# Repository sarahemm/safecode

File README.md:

safecode
========

SafeCode check-in system

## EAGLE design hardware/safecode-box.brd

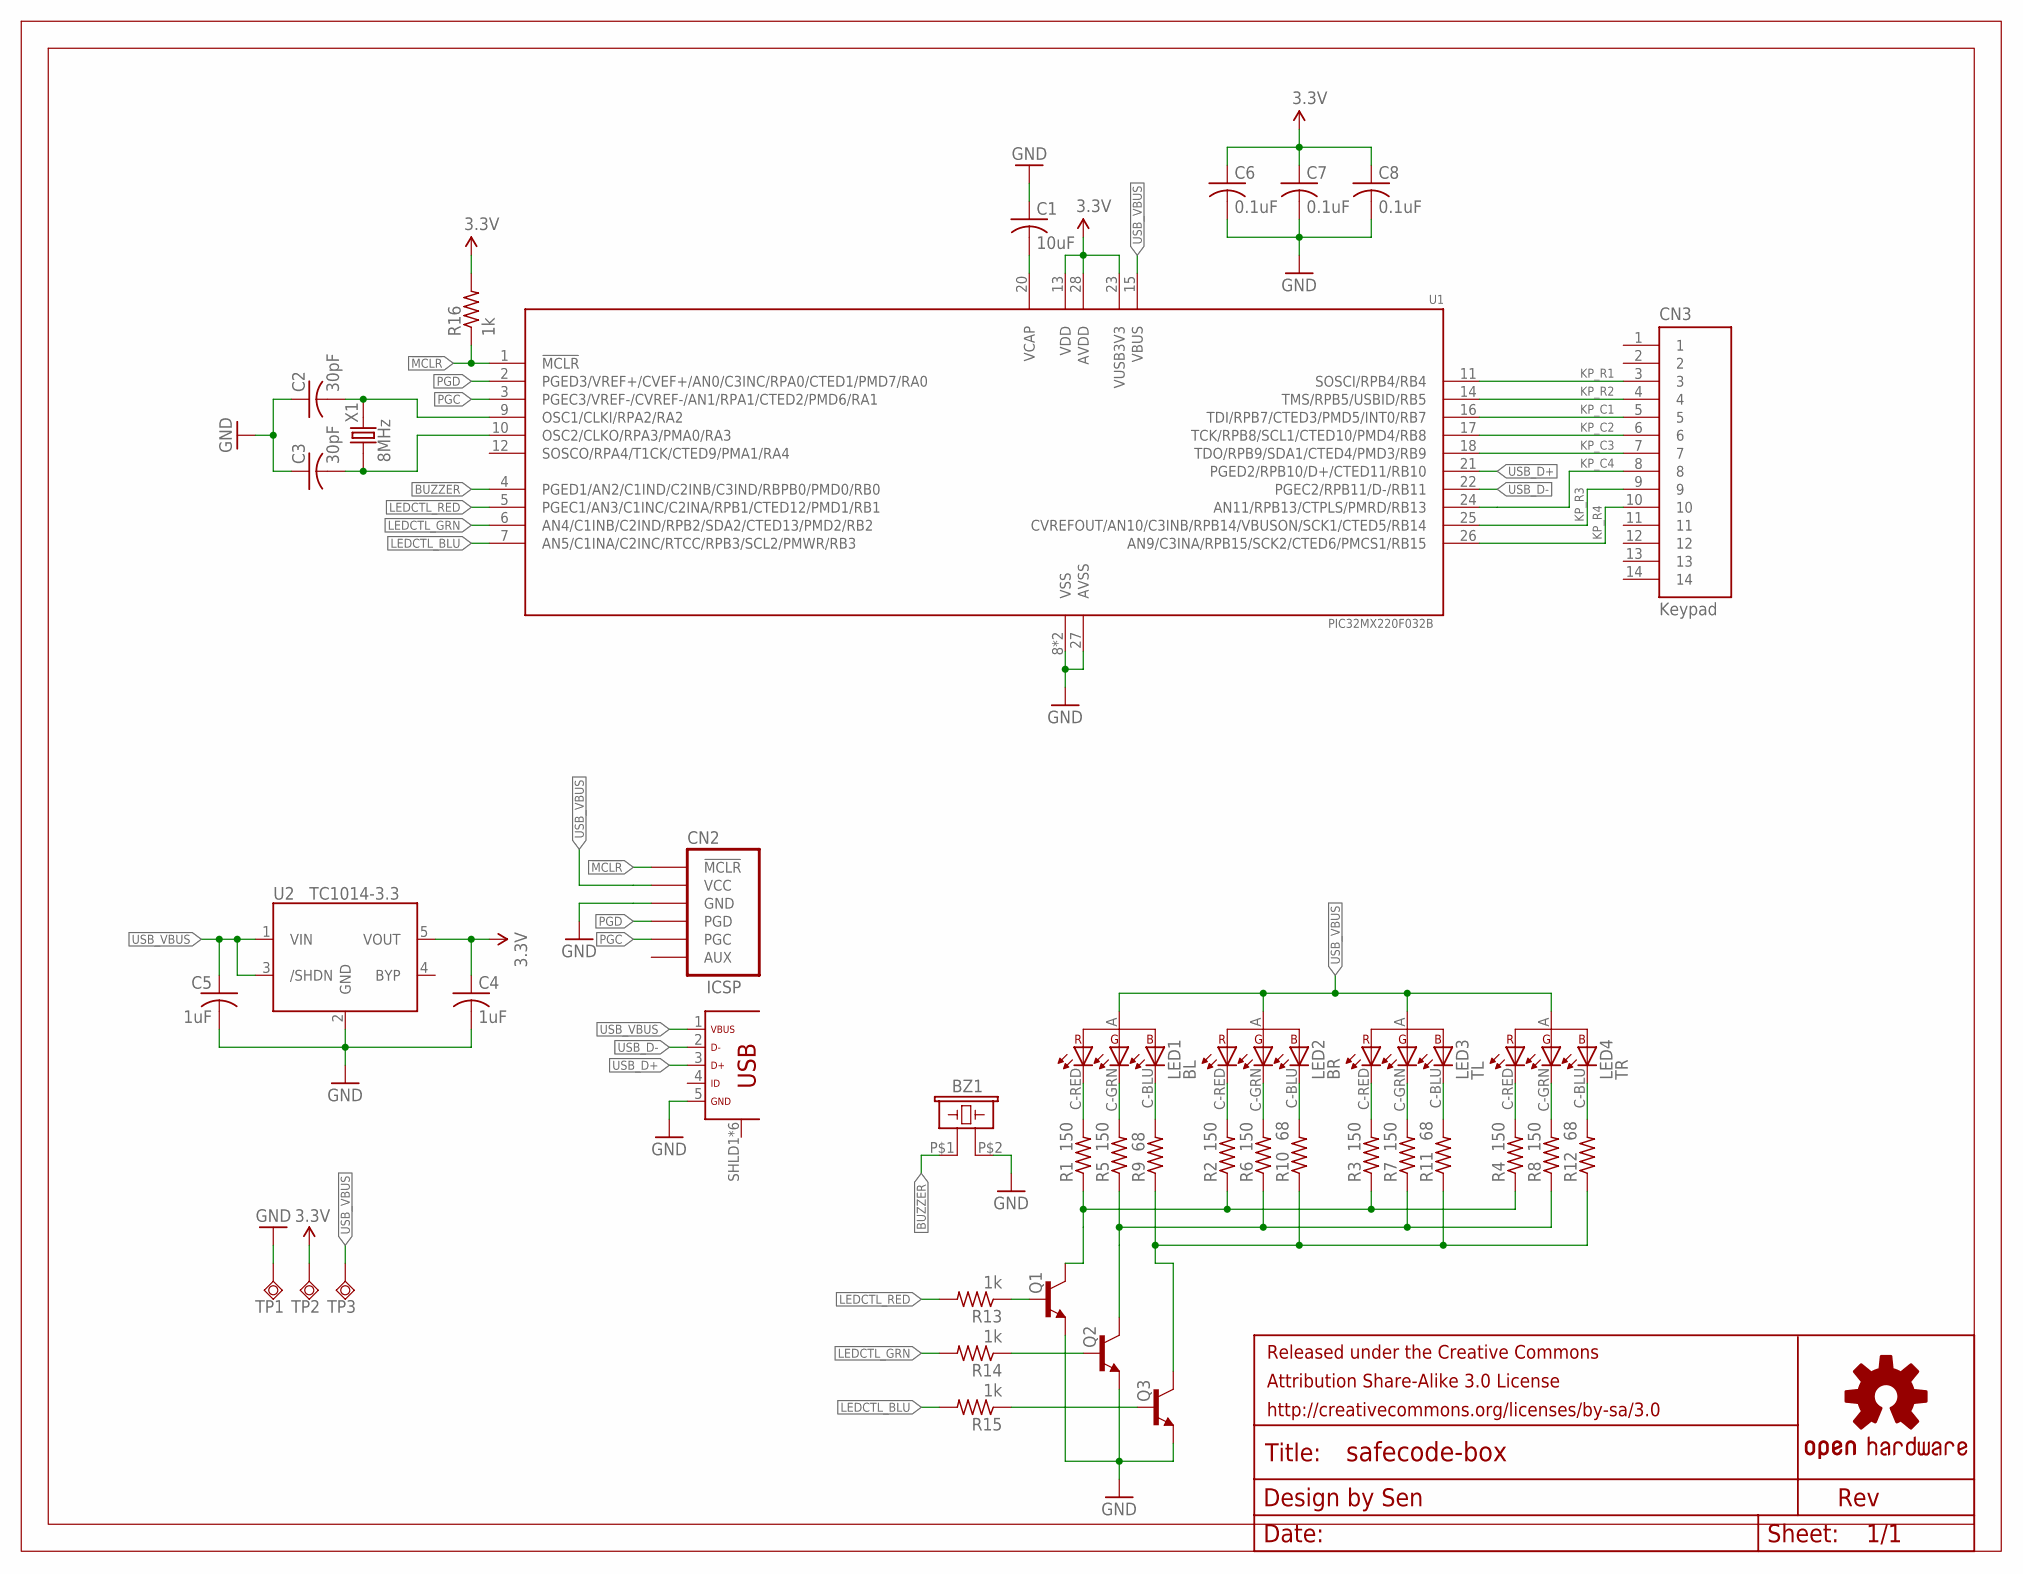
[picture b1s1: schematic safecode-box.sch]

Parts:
BZ1: CMD-1603-SMD; CMT-1603-SMD
C1: 10uF; C0805
C2, C3: 30pF; C0603
C4, C5: 1uF; C0603
C6, C7, C8: 0.1uF; C0603
CN1: FCI-10118192-MICROUSB
CN2: ICSP; ICSP-6PAD
CN3: Keypad; 3M-963114
FRAME1: FRAME-LETTER-GRID-OSHW-SENOSHW-LOGO-L; OSHW-LOGO-L
LED1: BL; AVAGO-HSMF-C113/115
LED2: BR; AVAGO-HSMF-C113/115
LED3: TL; AVAGO-HSMF-C113/115
LED4: TR; AVAGO-HSMF-C113/115
Q1, Q2, Q3: MMBT3904; SOT23-BEC
R1, R2, R3, R4, R5, R6, R7, R8: 150; R0603
R9, R10, R11, R12: 68; R0603
R13, R14, R15, R16: 1k; R0603
TP1: GND; B2,54
TP2: 3.3V; B2,54
TP3: VBUS; B2,54
U1: PIC32MX220F032B; SO28W
U2: TC1014-3.3; SOT23-5
X1: 8MHz; NX8045GB

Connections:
3.3V: C4.1, C6.1, C7.1, C8.1, R16.2, TP2.TP, U1.13 (VDD), U1.23 (VUSB3V3), U1.28 (AVDD), U2.5 (VOUT)
!MCLR: CN2.!MCLR, R16.1, U1.1 (!MCLR)
BL-B-R: LED1.C-BLU, R9.2
BL-G-R: LED1.C-GRN, R5.2
BL-R-R: LED1.C-RED, R1.2
BR-B-R: LED2.C-BLU, R10.2
BR-G-R: LED2.C-GRN, R6.2
BR-R-R: LED2.C-RED, R2.2
BUZZER: BZ1.P$1 (1), U1.4 (PGED1/AN2/C1IND/C2INB/C3IND/RBPB0/PMD0/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)
GND: BZ1.P$2 (2), C1.1, C2.1, C3.1, C4.2, C5.2, C6.2, C7.2, C8.2, CN1.5 (GND), CN2.GND, Q1.E, Q2.E, Q3.E, TP1.TP, U1.8 (VSS), U1.19 (VSS), U1.27 (AVSS), U2.2 (GND)
KP_C1: CN3.5, U1.16 (TDI/RPB7/CTED3/PMD5/INT0/RB7)
KP_C2: CN3.6, U1.17 (TCK/RPB8/SCL1/CTED10/PMD4/RB8)
KP_C3: CN3.7, U1.18 (TDO/RPB9/SDA1/CTED4/PMD3/RB9)
KP_C4: CN3.8, U1.24 (AN11/RPB13/CTPLS/PMRD/RB13)
KP_R1: CN3.3, U1.11 (SOSCI/RPB4/RB4)
KP_R2: CN3.4, U1.14 (TMS/RPB5/USBID/RB5)
KP_R3: CN3.9, U1.25 (CVREFOUT/AN10/C3INB/RPB14/VBUSON/SCK1/C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)
KP_R4: CN3.10, U1.26 (AN9/C3INA/RPB15/SCK2/CTED6/PMCS1/RB15)
LEDCTL_BLU: R15.2, U1.7 (AN5/C1INA/C2INC/RTCC/RPB3/SCL2/PMWR/RB3)
LEDCTL_GRN: R14.2, U1.6 (AN4/C1INB/C2IND/RPB2/SDA2/CTED13/PMD2/R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)
LEDCTL_RED: R13.2, U1.5 (PGEC1/AN3/C1INC/C2INA/RPB1/CTED12/PMD1/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)
LED_C_BLU: Q3.C, R9.1, R10.1, R11.1, R12.1
LED_C_GRN: Q2.C, R5.1, R6.1, R7.1, R8.1
LED_C_RED: Q1.C, R1.1, R2.1, R3.1, R4.1
OSC1: C2.2, U1.9 (OSC1/CLKI/RPA2/RA2), X1.P$2 (2)
OSC2: C3.2, U1.10 (OSC2/CLKO/RPA3/PMA0/RA3), X1.P$1 (1)
PGC: CN2.PGC, U1.3 (PGEC3/VREF-/CVREF-/AN1/RPA1/CTED2/PMD6/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)
PGD: CN2.PGD, U1.2 (PGED3/VREF+/CVEF+/AN0/C3INC/RPA0/CTED1/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)
Q1-R: Q1.B, R13.1
Q2-R: Q2.B, R14.1
Q3-R: Q3.B, R15.1
TL-B-R: LED3.C-BLU, R11.2
TL-G-R: LED3.C-GRN, R7.2
TL-R-R: LED3.C-RED, R3.2
TR-B-R: LED4.C-BLU, R12.2
TR-G-R: LED4.C-GRN, R8.2
TR-R-R: LED4.C-RED, R4.2
USB_D+: CN1.3 (D+), U1.21 (PGED2/RPB10/D+/CTED11/RB10)
USB_D-: CN1.2 (D-), U1.22 (PGEC2/RPB11/D-/RB11)
USB_VBUS: C5.1, CN1.1 (VBUS), CN2.VCC, LED1.A, LED2.A, LED3.A, LED4.A, TP3.TP, U1.15 (VBUS), U2.1 (VIN), U2.3 (/SHDN)
VCAP: C1.2, U1.20 (VCAP)

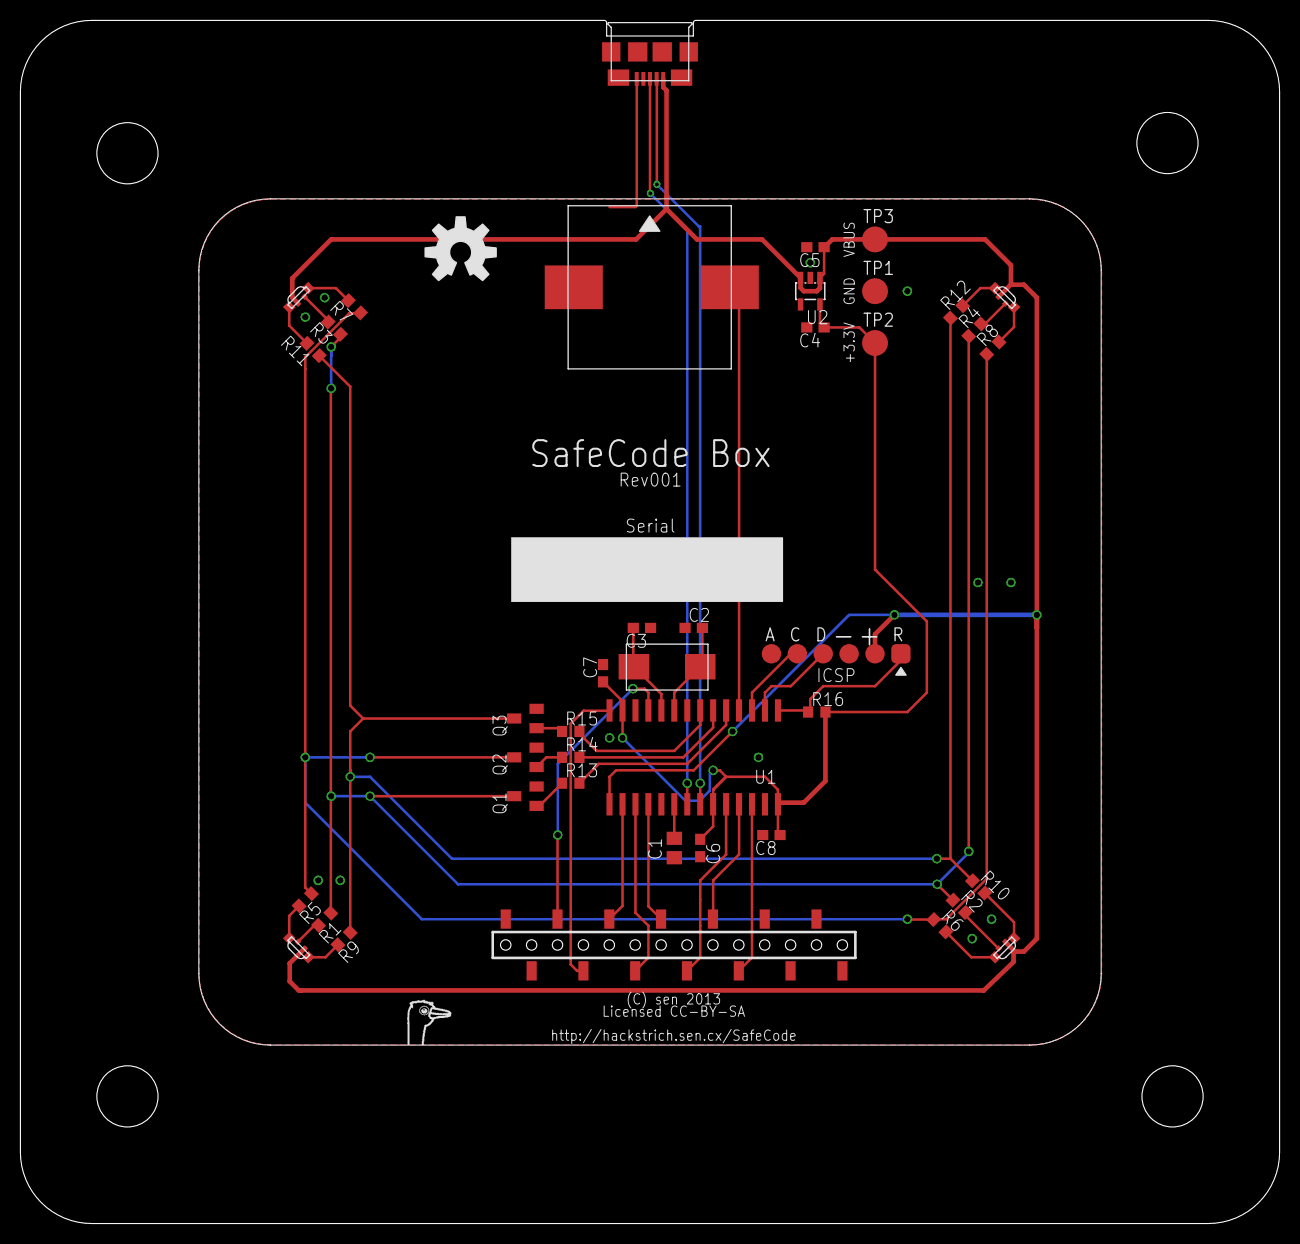
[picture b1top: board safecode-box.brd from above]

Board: 2 copper layers, 123.5 x 118.0 mm, 43 parts (0 on the bottom side), 41 nets.

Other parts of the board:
U$1: STRICH-LOGO-R

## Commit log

2013-06-03 Adding initial version of code. Still has a lot of work needing to be done, but web front-end works, talks to the webservice which talks to the daemon.
2013-06-03 Hardware interface code started, mostly working.
2013-06-04 Redid protocol between daemon and webservice to move all "business logic" into the webservice.
2013-06-04 Implemented client_arrived and check_out messages.
2013-06-05 Decoupled UI updates from packets being received (counter free-runs between updates) and added monitoring of last communication and warning for keepalive loss.
2013-06-05 Added alerting (bar turns red + text changes) when a check-in time is missed.
2013-06-05 Added reconnecting to the SafeCode box when the connection is lost. Next step is adding reporting of this status.
2013-06-08 Moved hardware drivers for the daemon to separate modules, including the existing prototype SafeCode Box plus a new terminal-based simulator for test/dev purposes.
2013-06-08 Fixing typo.
2013-06-08 Implemented responses from the web service to the daemon, so the box can have lighting indicating the state/last command status. All working in the simulator.
2013-06-09 Refactored code to use the statemachine gem, which makes invalid transitions impossble and makes the code easier to maintain.
2013-06-12 Added functionality to the tabs at the top, now an Update form is available that sends a JSON packet to the web service. No implementation on the webservice side yet.
2013-06-12 Fixed JSON-ization of location updates, added code to the webservice to actually update. Next step is to add auth for such.
2013-06-16 Added authentication of location updates, plus changed the UI/webservice to actually display the location.
2013-06-16 Moved FSM out of settings because it's not a setting, moved yubikey config info into a YAML config file.
2013-06-16 Changed to using the sinatra auto-config-file-loader rather than manually loading it.
2013-06-16 Added logic to check that the correct Yubikey is being used, and made it more resilient against invalid keys.
2013-06-16 Cleaned up notifications of monitor updates being sent.
2013-06-16 Now the frontend reconnects to the webservice if it becomes unavailable then comes back.
2013-06-19 Fixed crash when trying to execute invalid state transitions.
2013-06-19 Added driver for the real safecode box, and switched the daemon to using it. Prototype stack using the real keypad and test lighting/sound all working now.
2013-06-22 Removing printing of the seekrit code.
2013-06-22 Added keepalives between daemon and webservice, which also makes the error state clear after 1s :)
2013-06-22 Initial work on the schematic.
2013-06-22 Completed schematic including checklist.
2013-06-22 Placement complete, routing coming up.
2013-06-22 Initial safecode box spacer. Needs work.
2013-06-22 Routing done, mechanical design still needs finishing.
2013-06-23 Final(?) revision of the safecode box enclosure.
2013-06-23 Fixed bug where invalid codes still caused success when moving from pre_checkin to in_session.
2013-06-23 Fixed behaviour when box is disconnected. Now we don't crash, and we also reconnect properly once it comes back.
2013-06-26 Completed/checklisted board.
2013-06-26 Final CAM output for Rev001 of the SafeCode box.
2013-06-26 Fixed bug where session data wasn't cleared on session end. Also added alert being passed back to the daemon when time expires w/o a check-in.
2013-06-26 Added alerting when the webservice indicates a check-in was missed.
2013-07-13 Changed colours around to be nicer
2013-07-13 Added audio alert support.
2013-07-16 Added support for a distress code, and moved codes into the config file.
2013-07-16 Moved duration formatting into a function and now supports hours.
2013-07-16 Fixing bug where daemon crashed if box was unplugged.
2013-07-20 Added functionality to monitor/report if the SafeCode box is unplugged.
2013-10-22 Bug fix, don't report the box as connected if we don't even have a connection to the room daemon.
2014-11-11 Added some extra debugging messages.
2014-11-11 Finally fixing bug where you have to pull up the web service in a browser before anything works from the box.

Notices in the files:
hardware/safecode-box.brd:
Licensed CC-BY-SA
parts and their libraries:
SparkFun: Licensing: CC v3.0 Share-Alike You are welcome to use this library for commercial purposes.
logos-sen: Released under the Creative Commons Attribution Share-Alike 3.0 License
logos-sen: http://creativecommons.org/licenses/by-sa/3.0
logos-sen: Released under the Creative Commons
